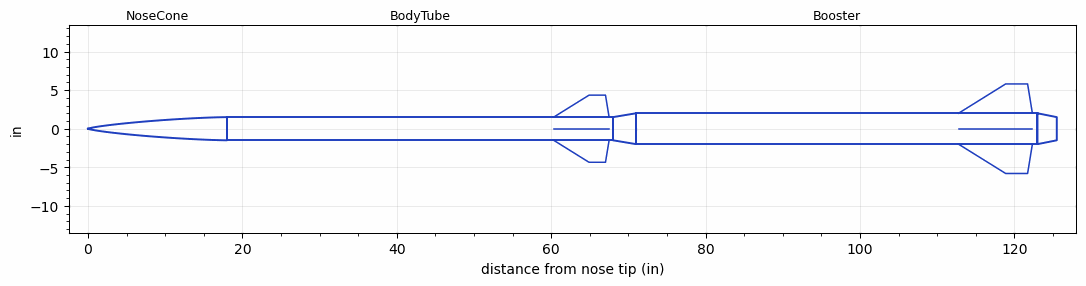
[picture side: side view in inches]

<RASAeroDocument>
 <FileVersion>2</FileVersion>
 <RocketDesign>
  <NoseCone>
   <Length>18</Length>
   <Diameter>3</Diameter>
   <Shape>Von Karman Ogive</Shape>
   <Location>0</Location>
  </NoseCone>
  <BodyTube>
   <Length>50</Length>
   <Diameter>3</Diameter>
   <Location>18</Location>
   <Fin>
    <Count>4</Count>
    <Chord>7.1775</Chord>
    <Span>2.85</Span>
    <SweepDistance>4.579</SweepDistance>
    <TipChord>2.13</TipChord>
    <Thickness>0.5</Thickness>
    <LERadius>0.08</LERadius>
    <Location>7.6725</Location>
    <AirfoilSection>Hexagonal</AirfoilSection>
    <FX1>0.5</FX1>
    <FX3>0.5</FX3>
   </Fin>
  </BodyTube>
  <Booster>
   <Length>52</Length>
   <Diameter>4</Diameter>
   <InsideDiameter>3</InsideDiameter>
   <Location>68</Location>
   <ShoulderLength>3</ShoulderLength>
   <BoattailLength>2.5</BoattailLength>
   <BoattailRearDiameter>3</BoattailRearDiameter>
   <Fin>
    <Count>4</Count>
    <Chord>9.57</Chord>
    <Span>3.8</Span>
    <SweepDistance>6.11</SweepDistance>
    <TipChord>2.84</TipChord>
    <Thickness>0.25</Thickness>
    <LERadius>0.08</LERadius>
    <Location>10.23</Location>
    <AirfoilSection>Hexagonal</AirfoilSection>
    <FX1>0.5</FX1>
    <FX3>0.5</FX3>
   </Fin>
  </Booster>
  <Surface>Cast Iron (Very Rough)</Surface>
  <ModifiedBarrowman>False</ModifiedBarrowman>
  <Turbulence>False</Turbulence>
  <UseBooster1>False</UseBooster1>
  <UseBooster2>False</UseBooster2>
 </RocketDesign>
 <LaunchSite>
  <Altitude>3000</Altitude>
  <Pressure>0</Pressure>
  <RodAngle>2</RodAngle>
  <RodLength>18</RodLength>
  <Temperature>85</Temperature>
  <WindSpeed>8</WindSpeed>
 </LaunchSite>
 <Recovery>
  <Altitude1>1000</Altitude1>
  <Altitude2>1000</Altitude2>
  <DeviceType1>None</DeviceType1>
  <DeviceType2>None</DeviceType2>
  <Event1>False</Event1>
  <Event2>False</Event2>
  <Size1>1</Size1>
  <Size2>1</Size2>
  <EventType1>None</EventType1>
  <EventType2>None</EventType2>
  <CD1>1.33</CD1>
  <CD2>1.33</CD2>
 </Recovery>
 <SimulationList>
  <Simulation>
   <SustainerEngine>M-1852  (M-1852)</SustainerEngine>
   <SustainerLaunchWt>24</SustainerLaunchWt>
   <SustainerNozzleDiameter>2.8</SustainerNozzleDiameter>
   <SustainerCG>34.07</SustainerCG>
   <SustainerIgnitionDelay>5</SustainerIgnitionDelay>
   <Booster1Engine>N-2712  (N-2712)</Booster1Engine>
   <Booster1LaunchWt>60.4</Booster1LaunchWt>
   <Booster1SeparationDelay>0</Booster1SeparationDelay>
   <Booster1IgnitionDelay>0</Booster1IgnitionDelay>
   <Booster1CG>56.47</Booster1CG>
   <Booster1NozzleDiameter>2.41</Booster1NozzleDiameter>
   <IncludeBooster1>True</IncludeBooster1>
   <Booster2Delay>0</Booster2Delay>
   <IncludeBooster2>False</IncludeBooster2>
   <TimetoApogee>53.59772</TimetoApogee>
   <MaxAltitude>46613.15</MaxAltitude>
   <MaxVelocity>2688.083</MaxVelocity>
  </Simulation>
 </SimulationList>
</RASAeroDocument>
